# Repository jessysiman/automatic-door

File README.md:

# Automatic door
The components used in this project are the ATMega8-16P microcontroller, the
TSSP58038 infrared sensor, two LEDs, the L298 motor driver, batteries and socket, a dc-motor,
and a couple of resistors, capacitors, and a 16MHz crystal. This system works by first having the
infrared sensor detect any signs of an object near the system. Afterwards, the sensor sends the
analog signal to the ATMega8 microcontroller for it to process it. If there is an object/living
being detected, the ATMega8 will tell the motor driver to rotate the dc-motor counterclockwise
to open the door. Then, when there is no object detected for around 5 seconds, the motor driver
will have the dc-motor rotate clockwise to close the door. Additionally, there are also LEDs that
will signify if the door is opened or closed.

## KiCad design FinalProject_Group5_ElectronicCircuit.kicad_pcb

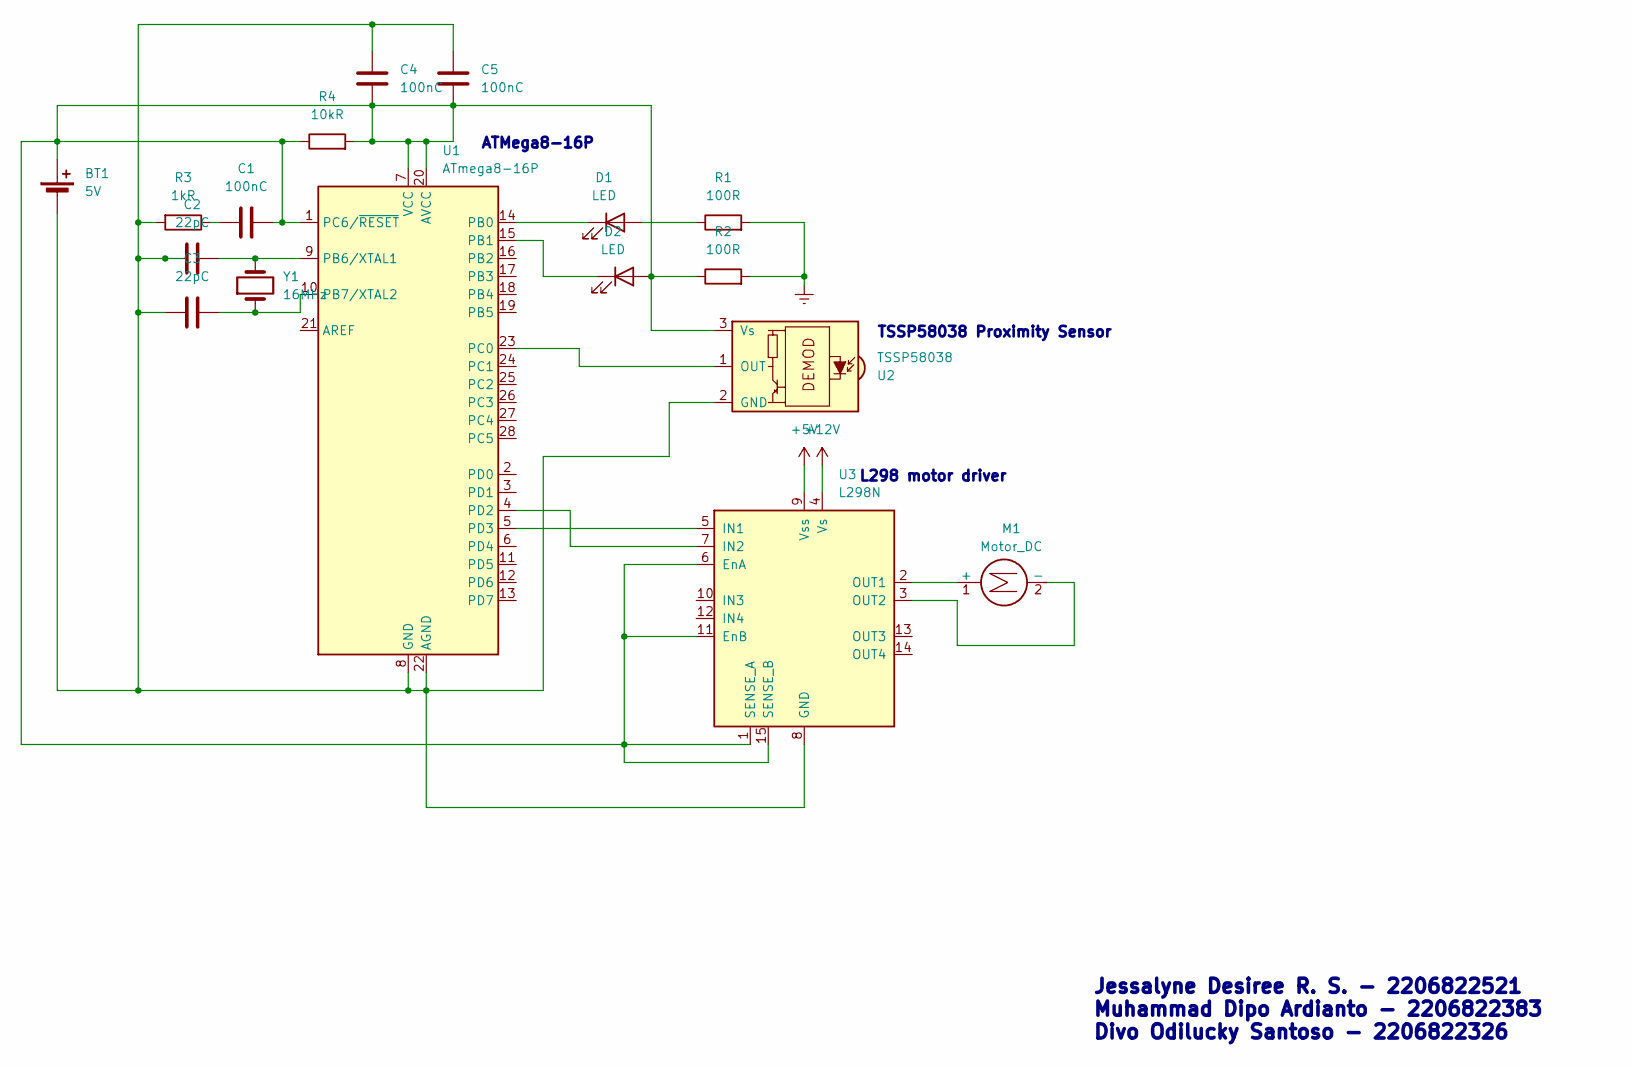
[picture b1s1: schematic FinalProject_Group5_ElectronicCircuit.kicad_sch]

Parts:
BT1: 5V; BatteryHolder_Keystone_2468_2xAAA
C1, C4, C5: 100nC; C_0603_1608Metric
C2, C3: 22pC; C_0603_1608Metric
D1, D2: LED; LED_D5.0mm_FlatTop
M1: Motor_DC; PinHeader_1x02_P2.54mm_Vertical
R1, R2: 100R; R_0603_1608Metric
R3: 1kR; R_0603_1608Metric
R4: 10kR; R_0603_1608Metric
U1: ATmega8-16P; DIP-28_W7.62mm
U2: TSSP58038; Vishay_MINICAST-3Pin
U3: L298N; TO-220-15_P2.54x2.54mm_StaggerOdd_Lead4.58mm_Vertical
Y1: 16MHz; Crystal_HC50_Vertical

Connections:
+5V: U3.9 (Vss)
+12V: U3.4 (Vs)
Earth: R1.2, R2.2
unnamed: BT1.1 (+), C1.2, C4.2, C5.2, D2.2 (A), R2.1, R4.1, R4.2, U1.1 (PC6/~RESET), U1.7 (VCC), U1.20 (AVCC), U2.3 (Vs), U3.1 (SENSE_A), U3.6 (EnA), U3.11 (EnB), U3.15 (SENSE_B)
unnamed: BT1.2 (-), C2.1, C3.1, C4.1, C5.1, R3.2, U1.8 (GND), U1.22 (AGND), U2.2 (GND), U3.8 (GND)
unnamed: C1.1, R3.1
unnamed: D1.2 (A), R1.1
unnamed: D1.1 (K), U1.14 (PB0)
unnamed: D2.1 (K), U1.15 (PB1)
unnamed: M1.1 (+), U3.2 (OUT1)
unnamed: M1.2 (-), U3.3 (OUT2)
unnamed: C2.2, U1.9 (PB6/XTAL1), Y1.2
unnamed: C3.2, U1.10 (PB7/XTAL2), Y1.1
unnamed: U1.23 (PC0), U2.1 (OUT)
unnamed: U1.4 (PD2), U3.7 (IN2)
unnamed: U1.5 (PD3), U3.5 (IN1)

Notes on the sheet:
Jessalyne Desiree R. S. - 2206822521 Muhammad Dipo Ardianto - 2206822383 Divo Odilucky Santoso - 2206822326
ATMega8-16P
TSSP58038 Proximity Sensor
L298 motor driver

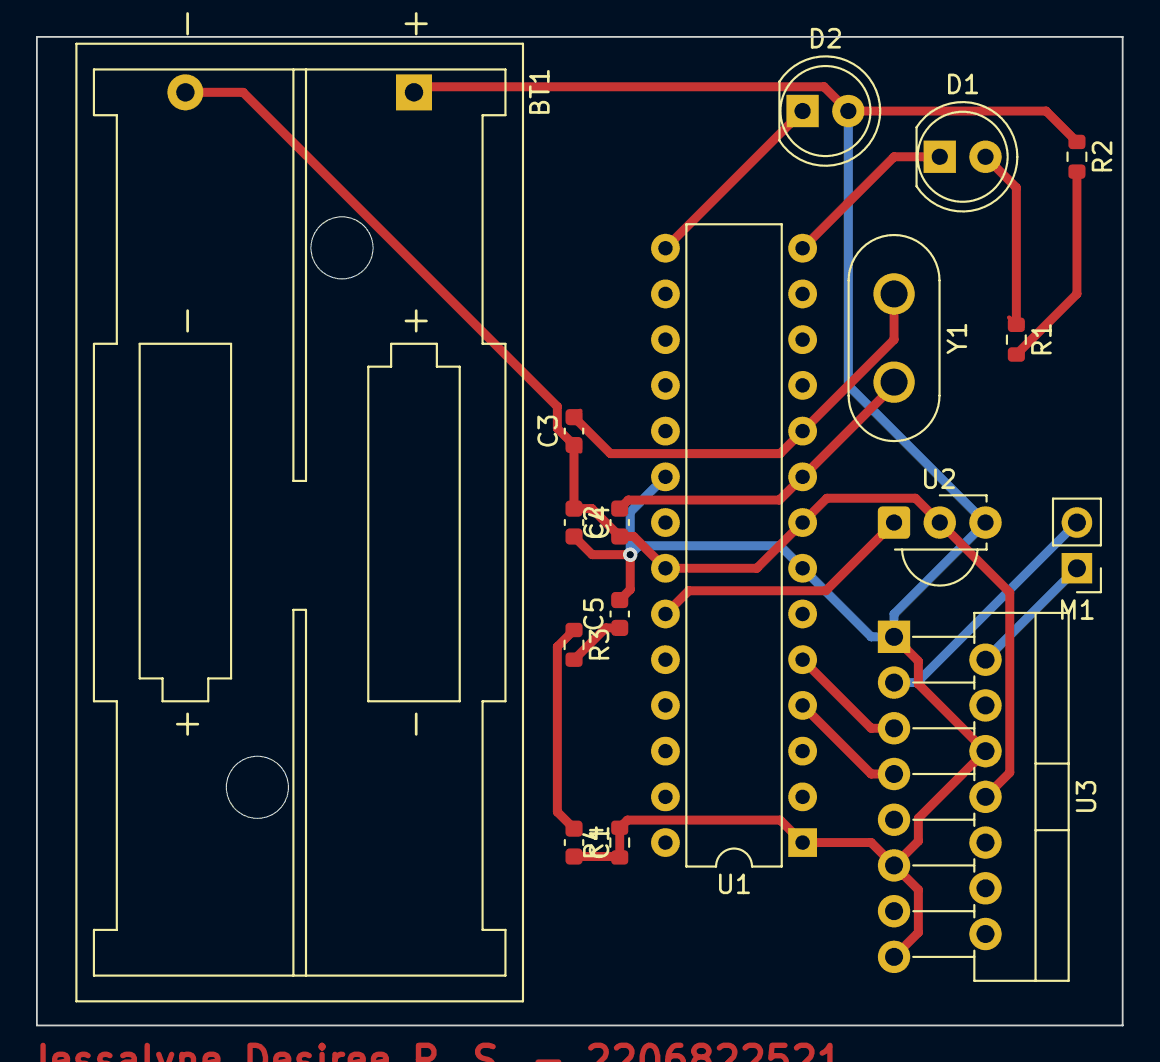
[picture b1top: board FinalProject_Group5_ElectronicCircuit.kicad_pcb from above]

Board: 2 copper layers, 60.3 x 54.9 mm, 17 parts (0 on the bottom side), 14 nets.
